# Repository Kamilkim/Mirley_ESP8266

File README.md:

# Mirley_ESP8266
Board to connect ESP8266 module to testing board mirley

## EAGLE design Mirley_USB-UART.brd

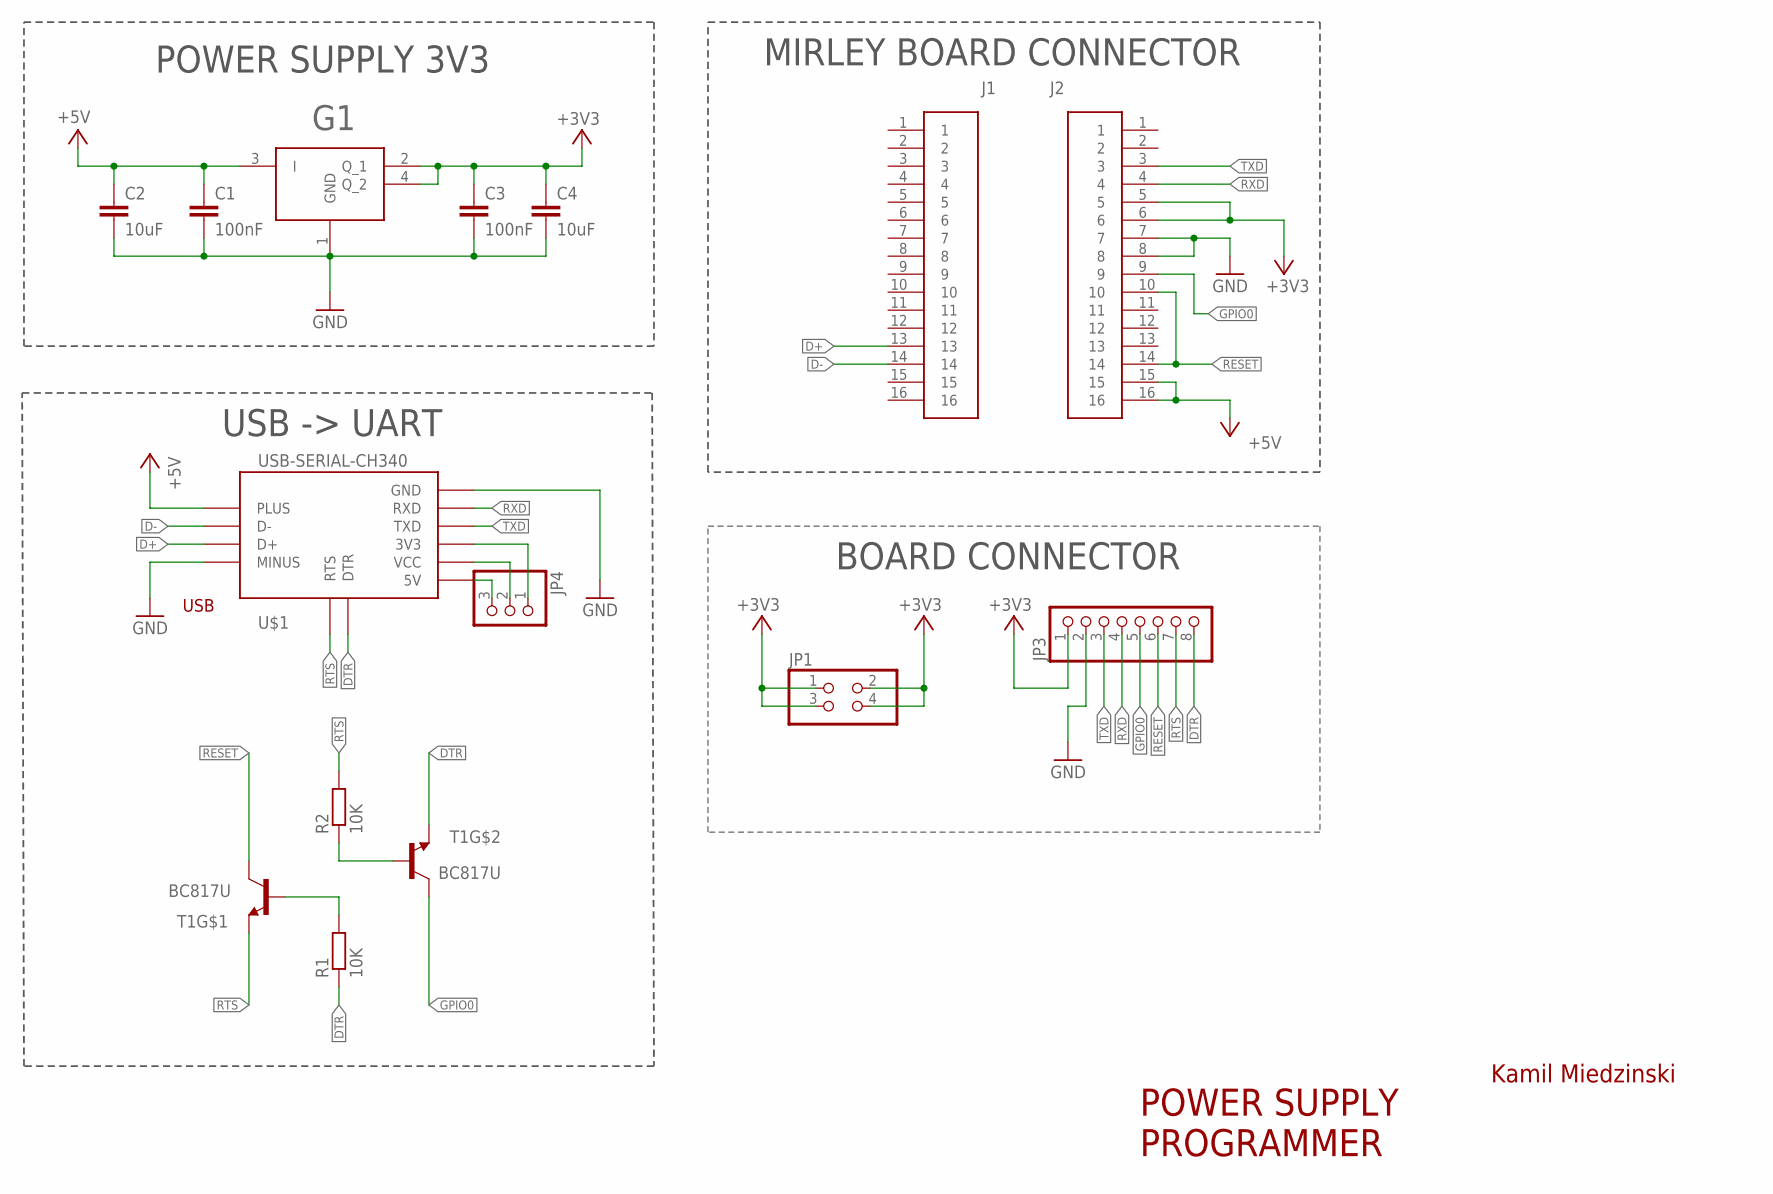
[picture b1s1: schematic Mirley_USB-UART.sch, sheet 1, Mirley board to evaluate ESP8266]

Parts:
C1, C3: 100nF; C0805K
C2, C4: 10uF; C0805K
G1: IFX1117ME_V33; SOT230P700X170-4N-1
J1, J2: 61301611121
JP1: PINHD-2X2; 2X02
JP3: PINHD-1X8; 1X08
JP4: PINHD-1X3; 1X03
R1, R2: 10K; R0805
T1: BC817U; INF-SC74
U$1: USB-SERIAL-CH340

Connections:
+3V3: C3.1, C4.1, G1.2 (Q_1), G1.4 (Q_2), J2.5, J2.6, JP1.1, JP1.2, JP1.3, JP1.4, JP3.1; also elsewhere on the board
+5V: C1.1, C2.1, G1.3 (I), J2.15, J2.16, U$1.PLUS; also elsewhere on the board
D+: J1.13, U$1.D+
D-: J1.14, U$1.D-
DTR: JP3.8, R1.1, T1.4 (E), U$1.DTR
GND: C1.2, C2.2, C3.2, C4.2, G1.1 (GND), J2.7, J2.8, JP3.2, U$1.GND, U$1.MINUS; also elsewhere on the board
GPIO0: J2.9, JP3.5, T1.3 (C); also elsewhere on the board
unnamed: R2.1, T1.5 (B)
unnamed: R1.2, T1.2 (B)
unnamed: JP4.3, U$1.5V
unnamed: JP4.2, U$1.VCC
unnamed: JP4.1, U$1.3V3
RESET: J2.10, J2.14, JP3.6, T1.6 (C); also elsewhere on the board
RTS: JP3.7, R2.2, T1.1 (E), U$1.RTS
RXD: J2.4, JP3.4, U$1.RXD; also elsewhere on the board
TXD: J2.3, JP3.3, U$1.TXD; also elsewhere on the board

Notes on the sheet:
Kamil Miedzinski
USB -> UART
POWER SUPPLY 3V3
MIRLEY BOARD CONNECTOR
POWER SUPPLY PROGRAMMER
BOARD CONNECTOR

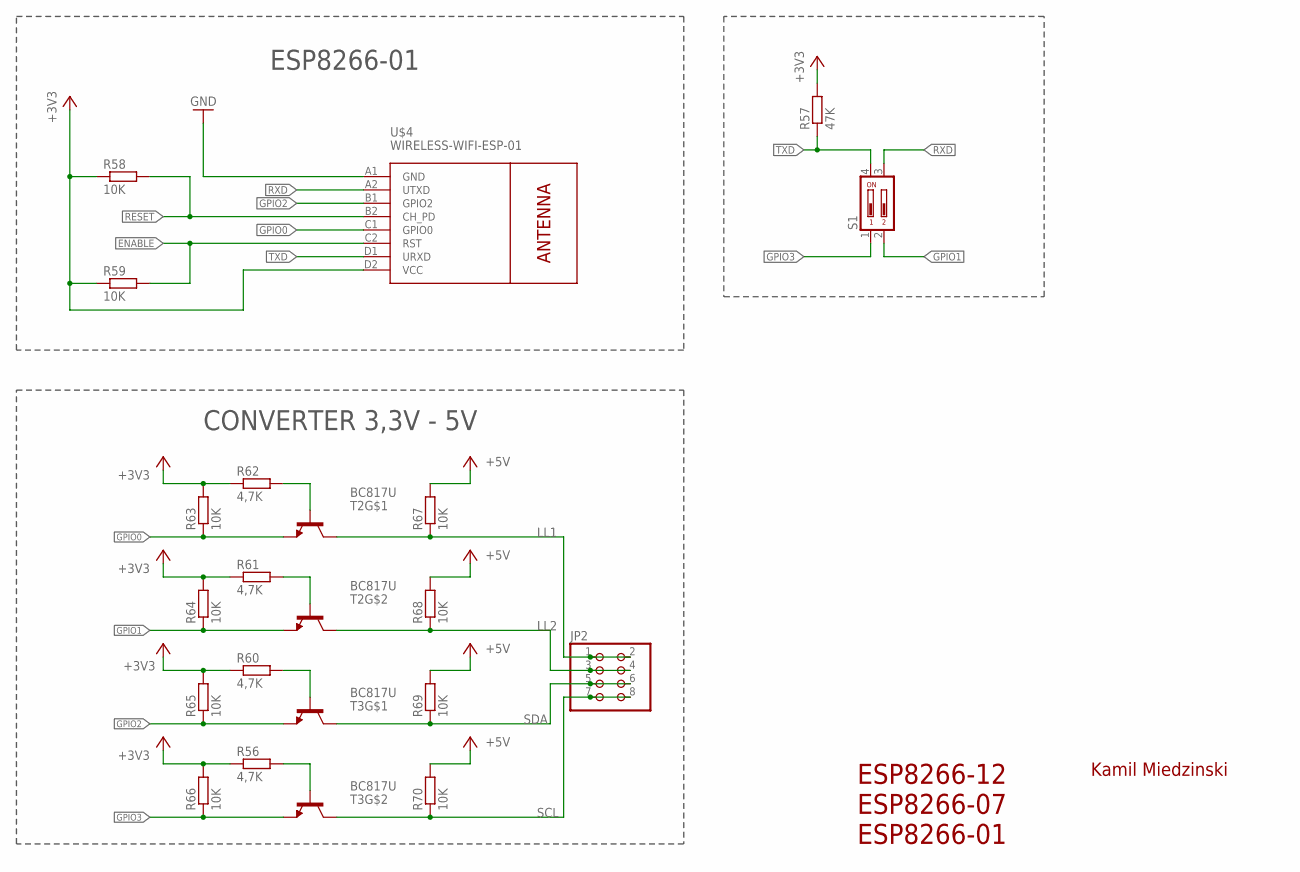
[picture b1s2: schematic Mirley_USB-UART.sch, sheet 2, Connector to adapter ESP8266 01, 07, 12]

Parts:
JP2: PINHD-2X4; 2X04
R56, R60, R61, R62: 4,7K; R0805
R57: 47K; R0805
R58, R59, R63, R64, R65, R66, R67, R68, R69, R70: 10K; R0805
S1: DIP02YL
T2, T3: BC817U; INF-SC74
U$4: WIRELESS-WIFI-ESP-01

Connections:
+3V3: R56.1, R57.2, R58.1, R59.1, R60.1, R61.1, R62.1, R63.2, R64.2, R65.2, R66.2, U$4.D2 (VCC); also elsewhere on the board
+5V: R67.2, R68.2, R69.2, R70.2; also elsewhere on the board
ENABLE: R59.2, U$4.C2 (RST)
GND: U$4.A1 (GND); also elsewhere on the board
GPIO0: R63.1, T2.1 (E), U$4.C1 (GPIO0); also elsewhere on the board
GPIO1: R64.1, S1.2, T2.4 (E)
GPIO2: R65.1, T3.1 (E), U$4.B1 (GPIO2)
GPIO3: R66.1, S1.1, T3.4 (E)
LL1: JP2.1, JP2.2, R67.1, T2.6 (C)
LL2: JP2.3, JP2.4, R68.1, T2.3 (C)
unnamed: R62.2, T2.2 (B)
unnamed: R61.2, T2.5 (B)
unnamed: R60.2, T3.2 (B)
unnamed: R56.2, T3.5 (B)
RESET: R58.2, U$4.B2 (CH_PD); also elsewhere on the board
RXD: S1.3, U$4.A2 (UTXD); also elsewhere on the board
SCL: JP2.7, JP2.8, R70.1, T3.3 (C)
SDA: JP2.5, JP2.6, R69.1, T3.6 (C)
TXD: R57.1, S1.4, U$4.D1 (URXD); also elsewhere on the board

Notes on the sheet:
Kamil Miedzinski
ESP8266-12 ESP8266-07 ESP8266-01
ESP8266-01
CONVERTER 3,3V - 5V

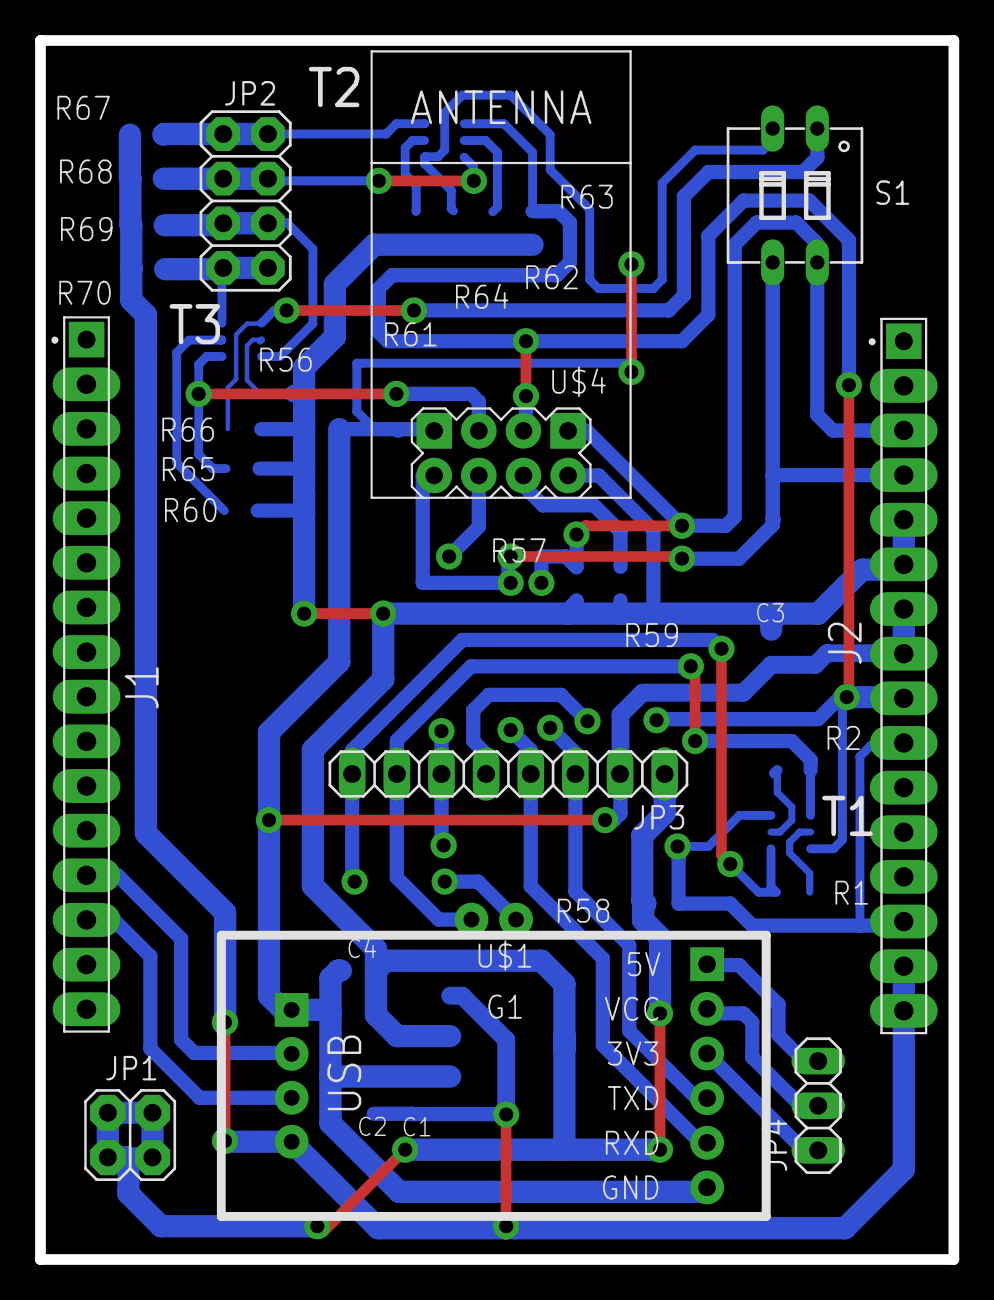
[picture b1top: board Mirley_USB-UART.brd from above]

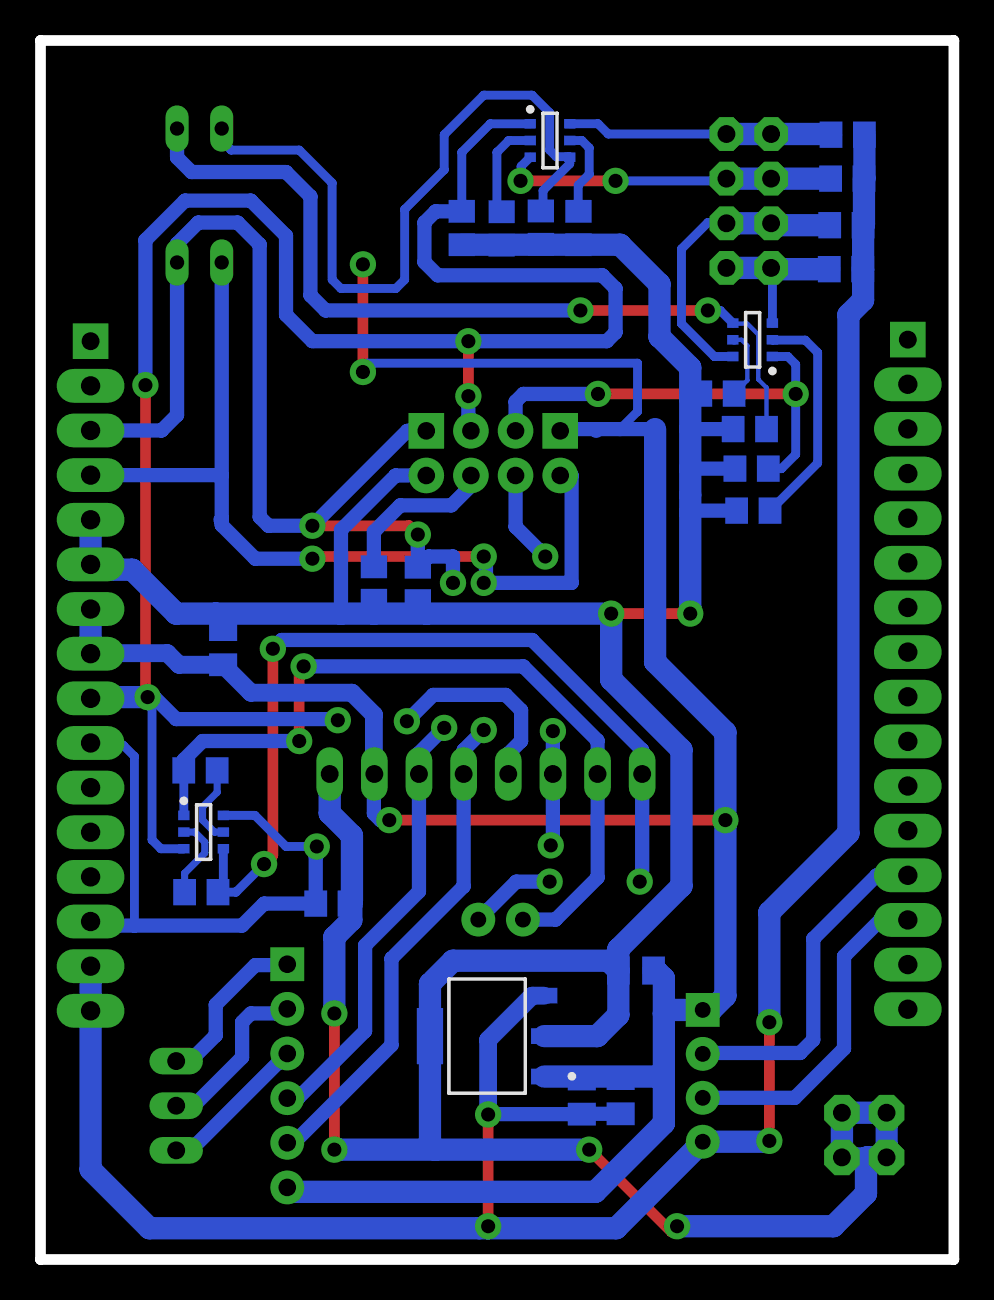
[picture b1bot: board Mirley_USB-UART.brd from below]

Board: 2 copper layers, 52.0 x 69.4 mm, 34 parts (25 on the bottom side), 28 nets.

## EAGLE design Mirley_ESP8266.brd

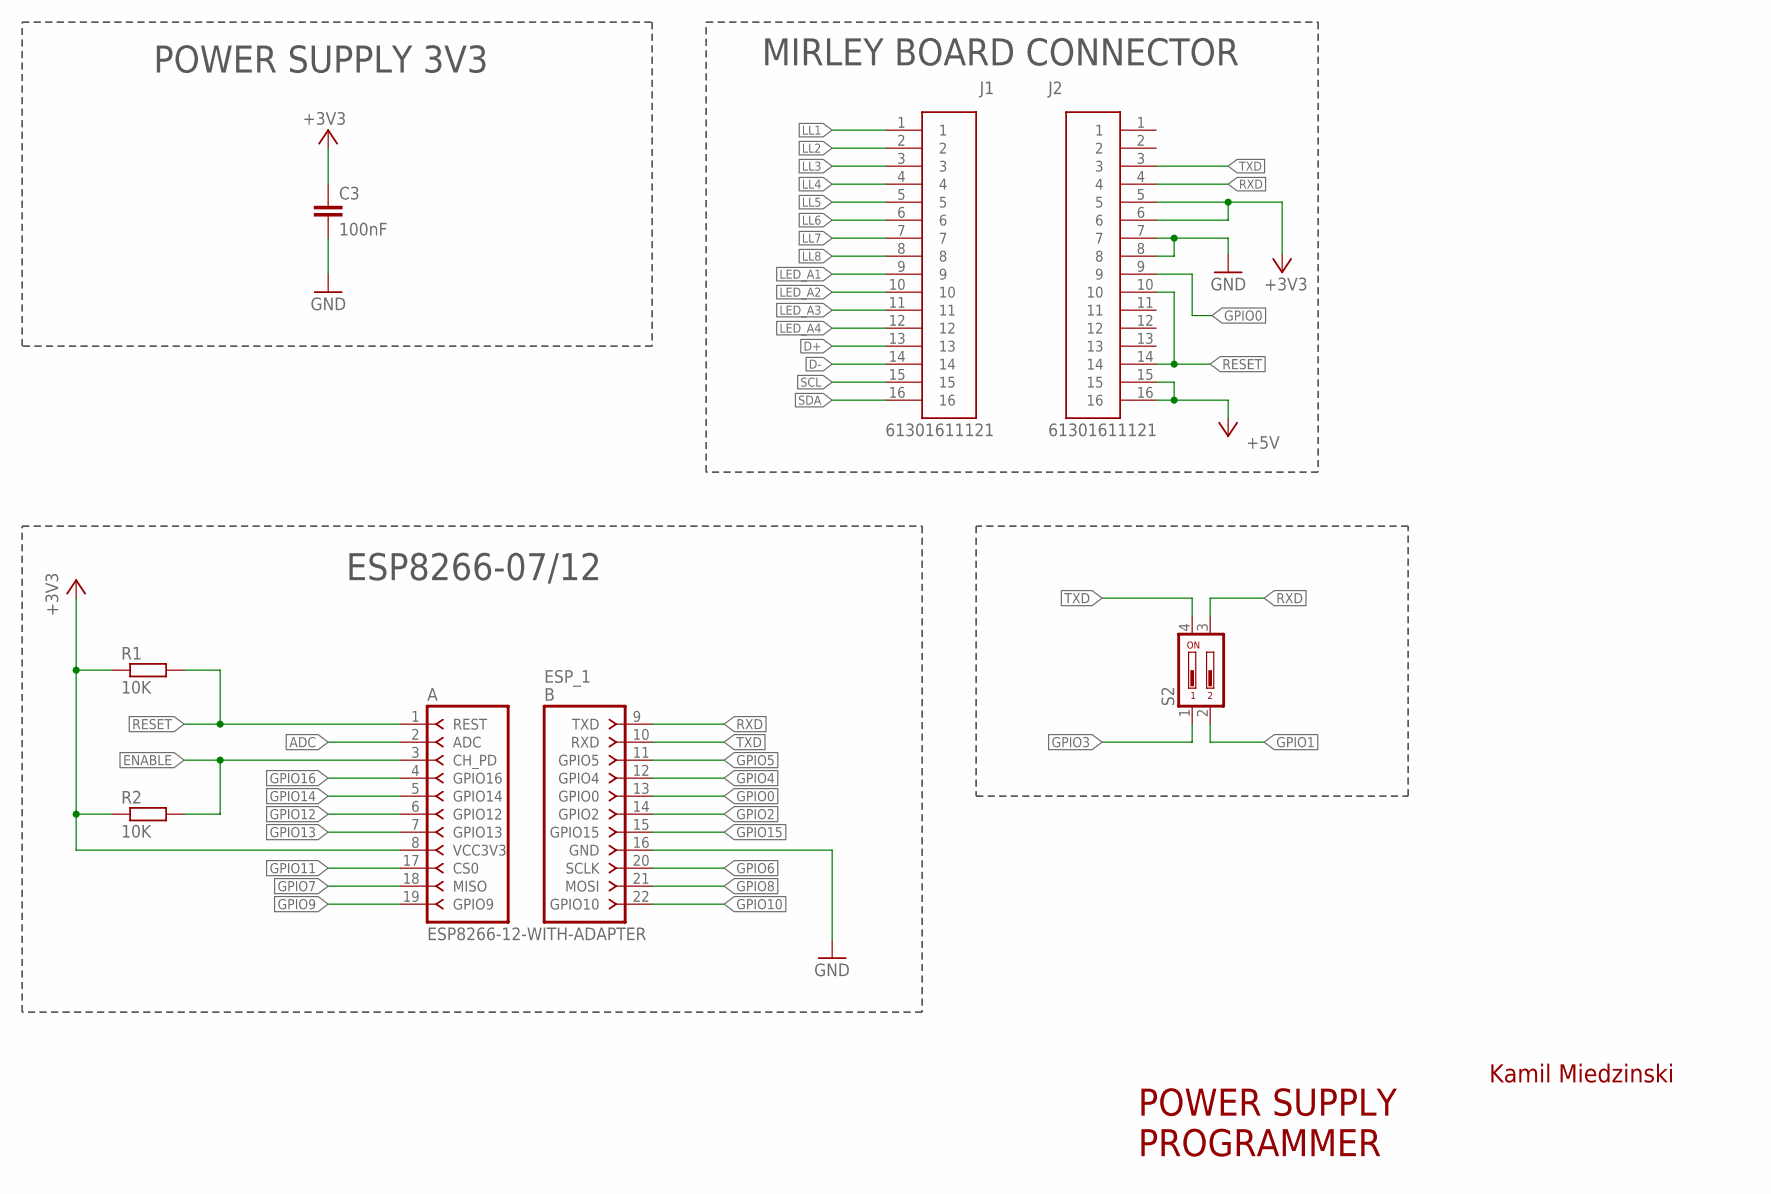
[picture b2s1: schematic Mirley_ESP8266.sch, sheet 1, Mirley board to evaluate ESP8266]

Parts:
C3: 100nF; C0805K
ESP_1: ESP8266-12-WITH-ADAPTER; ESP8266-12-ADAPTER
J1, J2: 61301611121
R1, R2: 10K; R0805
S2: DIP02YL

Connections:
+3V3: C3.1, ESP_1.8 (VCC3V3), J2.5, J2.6, R1.1, R2.1; also elsewhere on the board
+5V: J2.15, J2.16; also elsewhere on the board
ADC: ESP_1.2 (ADC); also elsewhere on the board
D+: J1.13
D-: J1.14
ENABLE: ESP_1.3 (CH_PD), R2.2; also elsewhere on the board
GND: C3.2, ESP_1.16 (GND), J2.7, J2.8; also elsewhere on the board
GPIO0: ESP_1.13 (GPIO0), J2.9; also elsewhere on the board
GPIO1: S2.2; also elsewhere on the board
GPIO2: ESP_1.14 (GPIO2); also elsewhere on the board
GPIO3: S2.1; also elsewhere on the board
GPIO4: ESP_1.12 (GPIO4); also elsewhere on the board
GPIO5: ESP_1.11 (GPIO5); also elsewhere on the board
GPIO6: ESP_1.20 (SCLK); also elsewhere on the board
GPIO7: ESP_1.18 (MISO); also elsewhere on the board
GPIO8: ESP_1.21 (MOSI); also elsewhere on the board
GPIO9: ESP_1.19 (GPIO9); also elsewhere on the board
GPIO10: ESP_1.22 (GPIO10); also elsewhere on the board
GPIO11: ESP_1.17 (CS0); also elsewhere on the board
GPIO12: ESP_1.6 (GPIO12); also elsewhere on the board
GPIO13: ESP_1.7 (GPIO13); also elsewhere on the board
GPIO14: ESP_1.5 (GPIO14); also elsewhere on the board
GPIO15: ESP_1.15 (GPIO15); also elsewhere on the board
GPIO16: ESP_1.4 (GPIO16); also elsewhere on the board
LED_A1: J1.9; also elsewhere on the board
LED_A2: J1.10; also elsewhere on the board
LED_A3: J1.11; also elsewhere on the board
LED_A4: J1.12; also elsewhere on the board
LL1: J1.1; also elsewhere on the board
LL2: J1.2; also elsewhere on the board
LL3: J1.3; also elsewhere on the board
LL4: J1.4; also elsewhere on the board
LL5: J1.5; also elsewhere on the board
LL6: J1.6; also elsewhere on the board
LL7: J1.7; also elsewhere on the board
LL8: J1.8; also elsewhere on the board
RESET: ESP_1.1 (REST), J2.10, J2.14, R1.2; also elsewhere on the board
RXD: ESP_1.9 (TXD), J2.4, S2.3
SCL: J1.15; also elsewhere on the board
SDA: J1.16; also elsewhere on the board
TXD: ESP_1.10 (RXD), J2.3, S2.4

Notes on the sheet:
Kamil Miedzinski
POWER SUPPLY 3V3
MIRLEY BOARD CONNECTOR
POWER SUPPLY PROGRAMMER
ESP8266-07/12

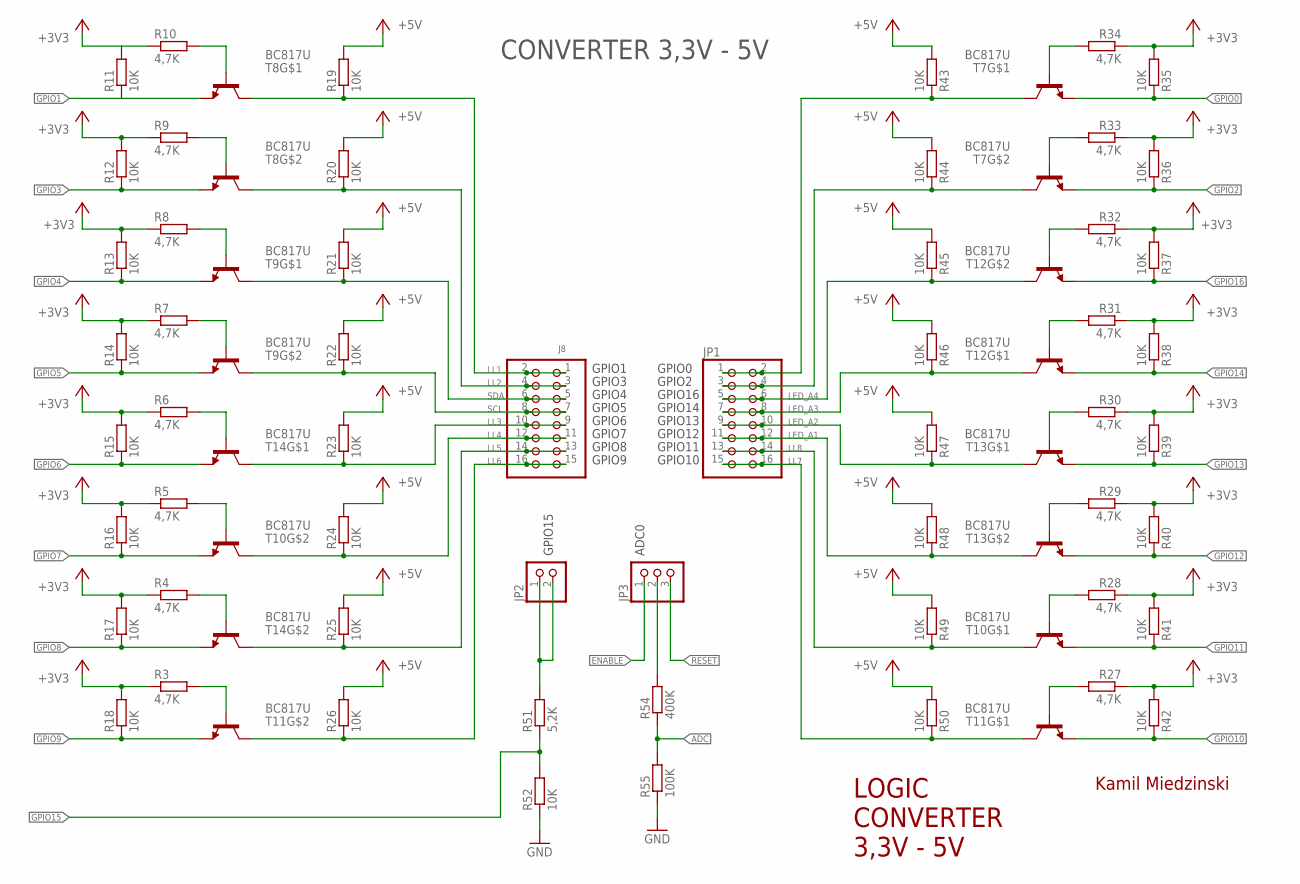
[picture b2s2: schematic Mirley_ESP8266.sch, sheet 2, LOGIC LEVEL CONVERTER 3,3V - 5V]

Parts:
J8: PINHD-2X8; 2X08
JP1: PINHD-2X8; 2X08
JP2: PINHD-1X2; 1X02
JP3: PINHD-1X3; 1X03
R3, R4, R5, R6, R7, R8, R9, R10, R27, R28, R29, R30, R31, R32, R33, R34: 4,7K; R0603
R11, R12, R13, R14, R15, R16, R17, R18, R19, R20, R21, R22, R23, R24, R25, R26, R35, R36, R37, R38, R39, R40, R41, R42, R43, R44, R45, R46, R47, R48, R49, R50, R52: 10K; R0805
R51: 5,2K; R0805
R54: 400K; R0805
R55: 100K; R0805
T7, T8, T9, T10, T11, T12, T13, T14: BC817U; INF-SC74

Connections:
+3V3: R3.1, R4.1, R5.1, R6.1, R7.1, R8.1, R9.1, R10.1, R11.2, R12.2, R13.2, R14.2, R15.2, R16.2, R17.2, R18.2, R27.1, R28.1, R29.1, R30.1, R31.1, R32.1, R33.1, R34.1, R35.2, R36.2, R37.2, R38.2, R39.2, R40.2, R41.2, R42.2; also elsewhere on the board
+5V: R19.2, R20.2, R21.2, R22.2, R23.2, R24.2, R25.2, R26.2, R43.2, R44.2, R45.2, R46.2, R47.2, R48.2, R49.2, R50.2; also elsewhere on the board
ADC: R54.1, R55.2; also elsewhere on the board
ENABLE: JP3.1; also elsewhere on the board
GND: R52.1, R55.1; also elsewhere on the board
GPIO0: R35.1, T7.1 (E); also elsewhere on the board
GPIO1: R11.1, T8.1 (E); also elsewhere on the board
GPIO2: R36.1, T7.4 (E); also elsewhere on the board
GPIO3: R12.1, T8.4 (E); also elsewhere on the board
GPIO4: R13.1, T9.1 (E); also elsewhere on the board
GPIO5: R14.1, T9.4 (E); also elsewhere on the board
GPIO6: R15.1, T14.1 (E); also elsewhere on the board
GPIO7: R16.1, T10.4 (E); also elsewhere on the board
GPIO8: R17.1, T14.4 (E); also elsewhere on the board
GPIO9: R18.1, T11.4 (E); also elsewhere on the board
GPIO10: R42.1, T11.1 (E); also elsewhere on the board
GPIO11: R41.1, T10.1 (E); also elsewhere on the board
GPIO12: R40.1, T13.4 (E); also elsewhere on the board
GPIO13: R39.1, T13.1 (E); also elsewhere on the board
GPIO14: R38.1, T12.1 (E); also elsewhere on the board
GPIO15: JP2.1, JP2.2, R51.1, R51.2, R52.2; also elsewhere on the board
GPIO16: R37.1, T12.4 (E); also elsewhere on the board
LED_A1: JP1.11, JP1.12, R48.1, T13.3 (C); also elsewhere on the board
LED_A2: JP1.9, JP1.10, R47.1, T13.6 (C); also elsewhere on the board
LED_A3: JP1.7, JP1.8, R46.1, T12.6 (C); also elsewhere on the board
LED_A4: JP1.5, JP1.6, R45.1, T12.3 (C); also elsewhere on the board
LL1: J8.1, J8.2, R19.1, T8.6 (C); also elsewhere on the board
LL2: J8.3, J8.4, R20.1, T8.3 (C); also elsewhere on the board
LL3: J8.9, J8.10, R23.1, T14.6 (C); also elsewhere on the board
LL4: J8.11, J8.12, R24.1, T10.3 (C); also elsewhere on the board
LL5: J8.13, J8.14, R25.1, T14.3 (C); also elsewhere on the board
LL6: J8.15, J8.16, R26.1, T11.3 (C); also elsewhere on the board
LL7: JP1.15, JP1.16, R50.1, T11.6 (C); also elsewhere on the board
LL8: JP1.13, JP1.14, R49.1, T10.6 (C); also elsewhere on the board
unnamed: JP1.3, JP1.4, R44.1, T7.3 (C)
unnamed: JP3.2, R54.2
unnamed: JP1.1, JP1.2, R43.1, T7.6 (C)
unnamed: R34.2, T7.2 (B)
unnamed: R10.2, T8.2 (B)
unnamed: R9.2, T8.5 (B)
unnamed: R33.2, T7.5 (B)
unnamed: R8.2, T9.2 (B)
unnamed: R32.2, T12.5 (B)
unnamed: R31.2, T12.2 (B)
unnamed: R7.2, T9.5 (B)
unnamed: R6.2, T14.2 (B)
unnamed: R30.2, T13.2 (B)
unnamed: R29.2, T13.5 (B)
unnamed: R5.2, T10.5 (B)
unnamed: R28.2, T10.2 (B)
unnamed: R4.2, T14.5 (B)
unnamed: R27.2, T11.2 (B)
unnamed: R3.2, T11.5 (B)
RESET: JP3.3; also elsewhere on the board
SCL: J8.7, J8.8, R22.1, T9.3 (C); also elsewhere on the board
SDA: J8.5, J8.6, R21.1, T9.6 (C); also elsewhere on the board

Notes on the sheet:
Kamil Miedzinski
CONVERTER 3,3V - 5V
LOGIC CONVERTER 3,3V - 5V
GPIO1
GPIO3
GPIO4
GPIO5
GPIO6
GPIO7
GPIO8
GPIO9
GPIO15
GPIO10
GPIO11
GPIO12
GPIO13
GPIO14
GPIO16
GPIO2
GPIO0
ADC0

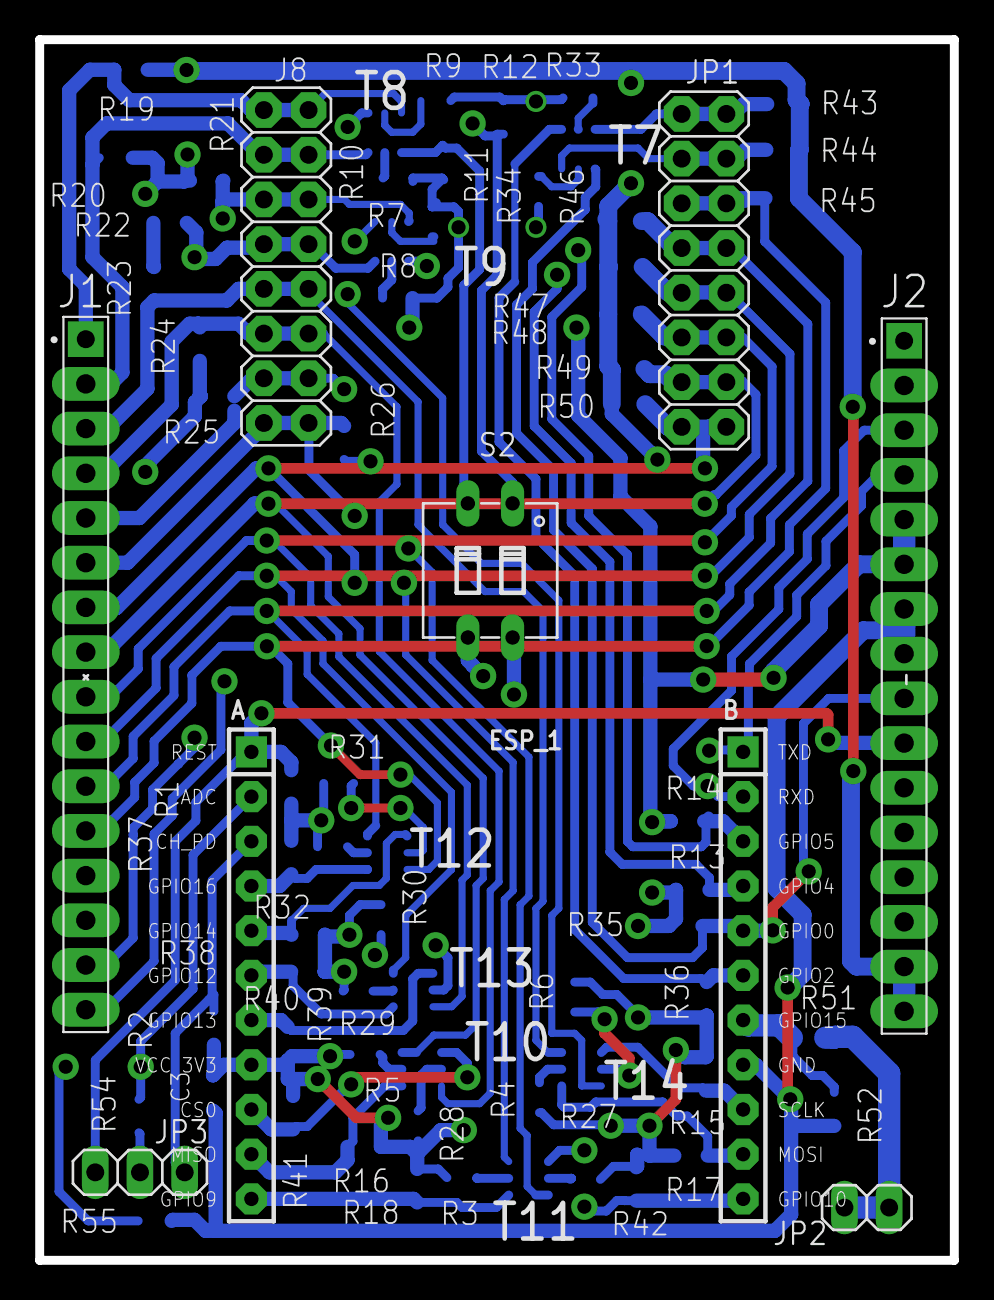
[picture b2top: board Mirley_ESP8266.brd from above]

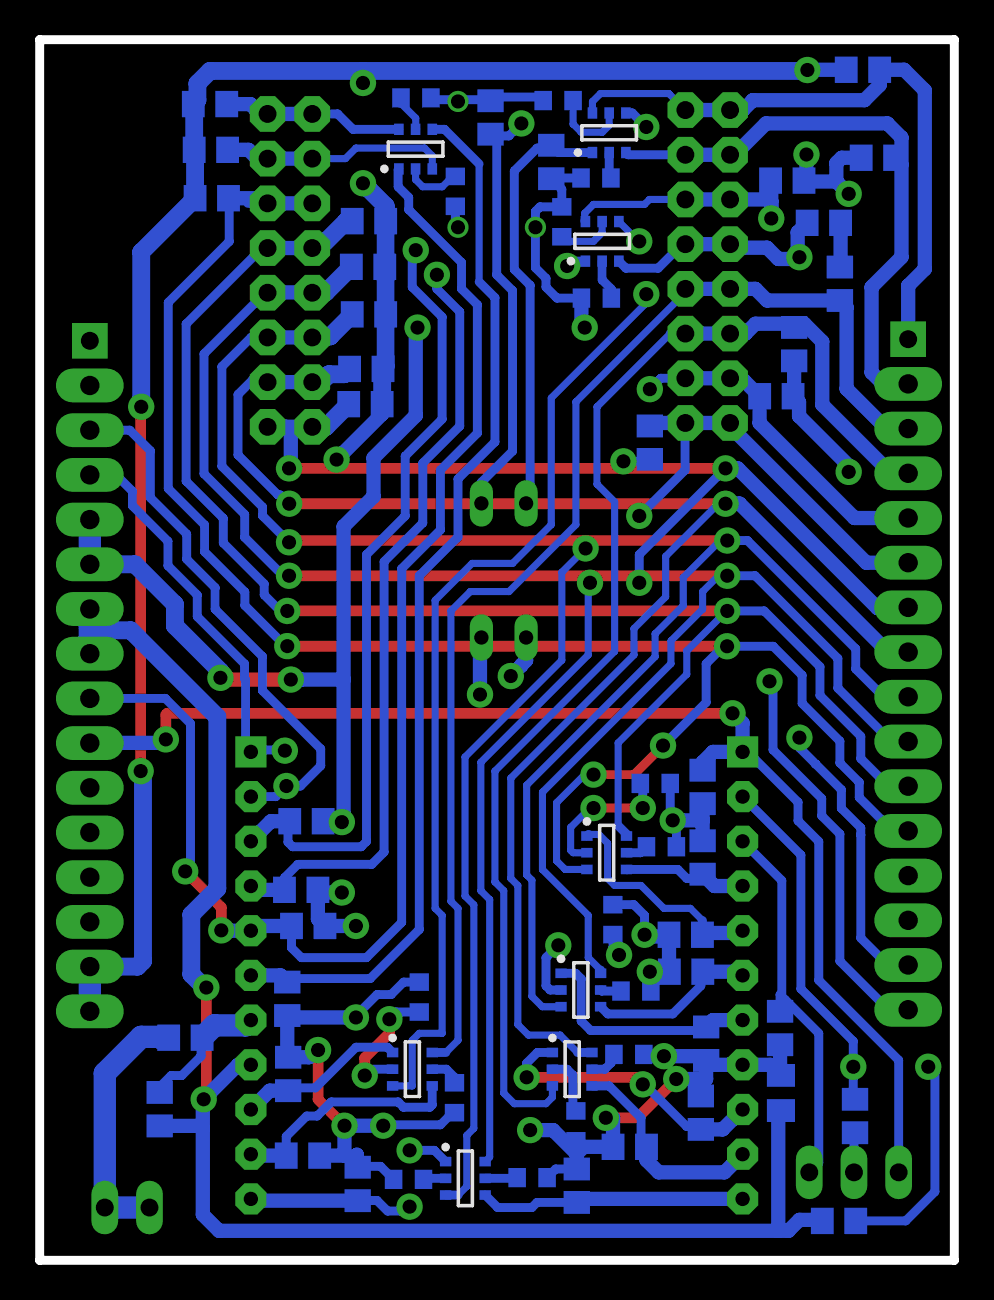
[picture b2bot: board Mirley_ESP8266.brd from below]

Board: 2 copper layers, 52.0 x 69.4 mm, 71 parts (63 on the bottom side), 58 nets.

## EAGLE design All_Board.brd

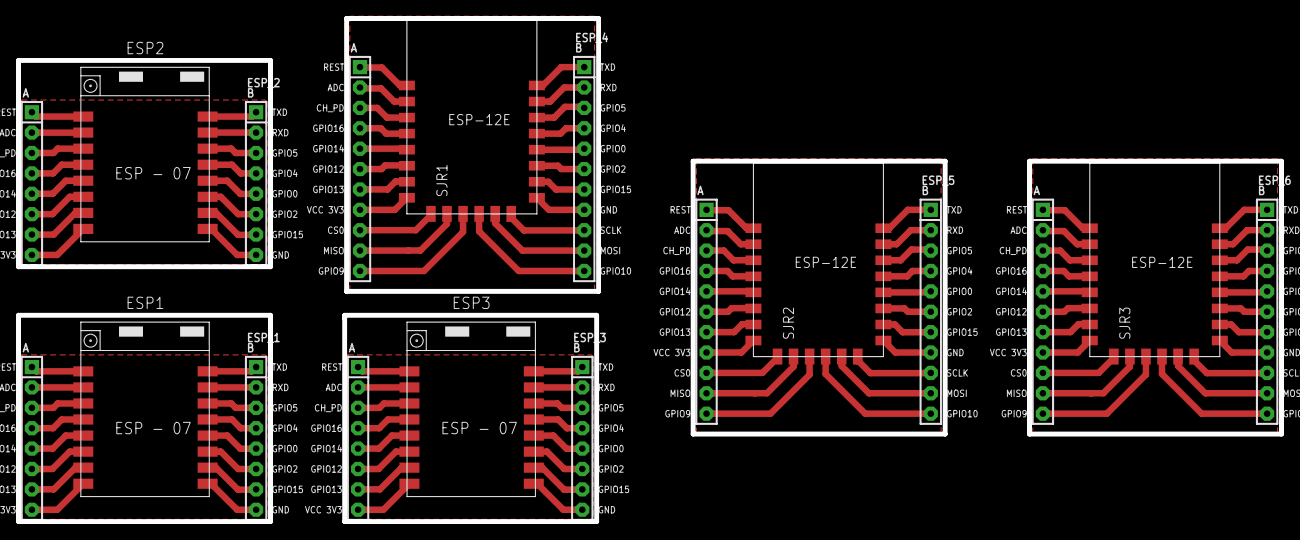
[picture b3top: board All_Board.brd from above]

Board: 2 copper layers, 157.4 x 62.7 mm, 12 parts (0 on the bottom side), 114 nets.

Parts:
ESP1, ESP2, ESP3: ESP8266-07SMT; ESP-07-SMT
ESP_1, ESP_2, ESP_3: ESP8266-WITH-ADAPTER; ESP8266-ADAPTER
ESP_4, ESP_5, ESP_6: ESP8266-12-WITH-ADAPTER; ESP8266-12-ADAPTER
SJR1, SJR2, SJR3: ESP8266-ESP12E

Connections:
ADC: ESP1.ADC, ESP_1.2
ADC1: ESP2.ADC, ESP_2.2
ADC2: ESP3.ADC, ESP_3.2
ADC3: ESP_4.2, SJR1.2
ADC4: ESP_5.2, SJR2.2
ADC5: ESP_6.2, SJR3.2
CH_PD: ESP1.EN, ESP_1.3
CH_PD1: ESP2.EN, ESP_2.3
CH_PD2: ESP3.EN, ESP_3.3
CH_PD3: ESP_4.3, SJR1.3
CH_PD4: ESP_5.3, SJR2.3
CH_PD5: ESP_6.3, SJR3.3
CS0: ESP_4.17, SJR1.17
CS1: ESP_5.17, SJR2.17
CS2: ESP_6.17, SJR3.17
GND: ESP1.GND, ESP_1.16
GND1: ESP2.GND, ESP_2.16
GND2: ESP3.GND, ESP_3.16
GND3: ESP_4.16, SJR1.9
GND4: ESP_5.16, SJR2.9
GND5: ESP_6.16, SJR3.9
GPIO0: ESP1.GPIO0, ESP_1.13
GPIO1: ESP2.GPIO16, ESP_2.4
GPIO2: ESP1.GPIO2, ESP_1.14
GPIO3: ESP2.GPIO14, ESP_2.5
GPIO4: ESP1.GPIO4, ESP_1.12
GPIO5: ESP1.GPIO5, ESP_1.11
GPIO6: ESP2.GPIO12, ESP_2.6
GPIO7: ESP2.GPIO13, ESP_2.7
GPIO8: ESP2.GPIO5, ESP_2.11
GPIO9: ESP2.GPIO4, ESP_2.12
GPIO10: ESP2.GPIO0, ESP_2.13
GPIO11: ESP2.GPIO2, ESP_2.14
GPIO12: ESP1.GPIO12, ESP_1.6
GPIO13: ESP1.GPIO13, ESP_1.7
GPIO14: ESP1.GPIO14, ESP_1.5
GPIO15: ESP1.GPIO15, ESP_1.15
GPIO16: ESP1.GPIO16, ESP_1.4
GPIO17: ESP2.GPIO15, ESP_2.15
GPIO18: ESP3.GPIO16, ESP_3.4
GPIO19: ESP3.GPIO14, ESP_3.5
GPIO20: ESP3.GPIO12, ESP_3.6
GPIO21: ESP3.GPIO13, ESP_3.7
GPIO22: ESP3.GPIO5, ESP_3.11
GPIO23: ESP3.GPIO4, ESP_3.12
GPIO24: ESP3.GPIO0, ESP_3.13
GPIO25: ESP3.GPIO2, ESP_3.14
GPIO26: ESP3.GPIO15, ESP_3.15
GPIO27: ESP_4.14, SJR1.11
GPIO28: ESP_4.11, SJR1.14
GPIO29: ESP_4.12, SJR1.13
GPIO30: ESP_4.13, SJR1.12
GPIO31: ESP_4.15, SJR1.10
GPIO32: ESP_4.22, SJR1.20
GPIO33: ESP_4.19, SJR1.19
GPIO34: ESP_4.4, SJR1.4
GPIO35: ESP_4.5, SJR1.5
GPIO36: ESP_4.7, SJR1.7
GPIO37: ESP_4.6, SJR1.6
GPIO38: ESP_5.14, SJR2.11
GPIO39: ESP_5.11, SJR2.14
GPIO40: ESP_5.12, SJR2.13
GPIO41: ESP_5.13, SJR2.12
GPIO42: ESP_5.15, SJR2.10
GPIO43: ESP_5.22, SJR2.20
GPIO44: ESP_5.19, SJR2.19
GPIO45: ESP_5.4, SJR2.4
GPIO46: ESP_5.5, SJR2.5
GPIO47: ESP_5.7, SJR2.7
GPIO48: ESP_5.6, SJR2.6
GPIO49: ESP_6.14, SJR3.11
GPIO50: ESP_6.11, SJR3.14
GPIO51: ESP_6.12, SJR3.13
GPIO52: ESP_6.13, SJR3.12
GPIO53: ESP_6.15, SJR3.10
GPIO54: ESP_6.22, SJR3.20
GPIO55: ESP_6.19, SJR3.19
GPIO56: ESP_6.4, SJR3.4
GPIO57: ESP_6.5, SJR3.5
GPIO58: ESP_6.7, SJR3.7
GPIO59: ESP_6.6, SJR3.6
MISO: ESP_4.18, SJR1.18
MISO1: ESP_5.18, SJR2.18
MISO2: ESP_6.18, SJR3.18
MOSI: ESP_4.21, SJR1.21
MOSI1: ESP_5.21, SJR2.21
MOSI2: ESP_6.21, SJR3.21
RESET: ESP1.RST, ESP_1.1
RESET1: ESP2.RST, ESP_2.1
RESET2: ESP3.RST, ESP_3.1
RESET3: ESP_4.1, SJR1.1
RESET4: ESP_5.1, SJR2.1
RESET5: ESP_6.1, SJR3.1
RXD: ESP1.RX, ESP_1.10
RXD1: ESP2.RX, ESP_2.10
RXD2: ESP3.RX, ESP_3.10
RXD3: ESP_4.10, SJR1.15
RXD4: ESP_5.10, SJR2.15
RXD5: ESP_6.10, SJR3.15
SCLK: ESP_4.20, SJR1.22
SCLK1: ESP_5.20, SJR2.22
SCLK2: ESP_6.20, SJR3.22
TXD: ESP1.TX, ESP_1.9
TXD1: ESP2.TX, ESP_2.9
TXD2: ESP3.TX, ESP_3.9
TXD3: ESP_4.9, SJR1.16
TXD4: ESP_5.9, SJR2.16
TXD5: ESP_6.9, SJR3.16
VCC: ESP1.VCC, ESP_1.8
VCC1: ESP2.VCC, ESP_2.8
VCC2: ESP3.VCC, ESP_3.8
VCC3: ESP_4.8, SJR1.8
VCC4: ESP_5.8, SJR2.8
VCC5: ESP_6.8, SJR3.8

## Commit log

2019-11-13 board chagned
2019-11-19 pierwsza wersja na jedenj plytce, niedokonczona
2019-11-19 druga wersja, dwie plytki
2019-11-20 pytlka programoatora w 50% narysowana
2019-11-21 programator zrobiony
2019-11-28 usb-uart skonczone, druga skonczona w 50%
2019-11-30 pierwsza docelowa wersja
2019-12-03 powiekszonyy odstepy miedzy sciezkami
2019-12-04 usuniete origin z top
2019-12-04 zmniejszona szerokosc sciezek pod tranzystorami

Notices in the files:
parts and their libraries:
diy-modules: Released under the Creative Commons Attribution 4.0 International License: http://creativecommons.org/licenses/by/4.0
